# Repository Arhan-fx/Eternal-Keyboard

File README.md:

I am trying to create a good keyboard that will be replacing my current keyboard, and I will try my best to use keyboard forever so thats why I am naming it "eterna keyboard".

My plan is recycle my old 60% keeb and slam a new pcb, keys, and keycaps to make it usable again.

BOM
| Name                                                          | Qty | Final Price - INR (USD) | Link                                                                                                       |
| ------------------------------------------------------------- | --- | ----------------------- | ---------------------------------------------------------------------------------------------------------- |
| Gateron Milky yellow pro (Pack of 10)                         | 70  | 1500 ($17.20)           | (https://www.keebsmod.com/products/gateron-milky-yellow-pro?variant=46478287733034)                                                    |
| Ussixchare Keycaps 60 Percent 104 Backlit                     | 1   | 2400 ($27.14)           | (https://www.amazon.in/Ussixchare-Keyboard-Fullsize-Mechanical-Switches/dp/B092DGKYR4?th=1)                         |
| Diode 1N4148 Through - Hole                                   | 100 | 169 ($1.97)             | (https://amzn.in/d/j3eLvoh)                                                                          
| Orpheus Pico                                                  | 1   | Already owned           |
| Case for keyboard                                             | 1   | Recycling from ant esports mk1300mini with mods |
| PCB                                                           | 1   |1550 (17.50)             | (https://hc-cdn.hel1.your-objectstorage.com/s/v3/194ccc0d3551b167a0d77d0481acf72b9a564b7d_image.png)

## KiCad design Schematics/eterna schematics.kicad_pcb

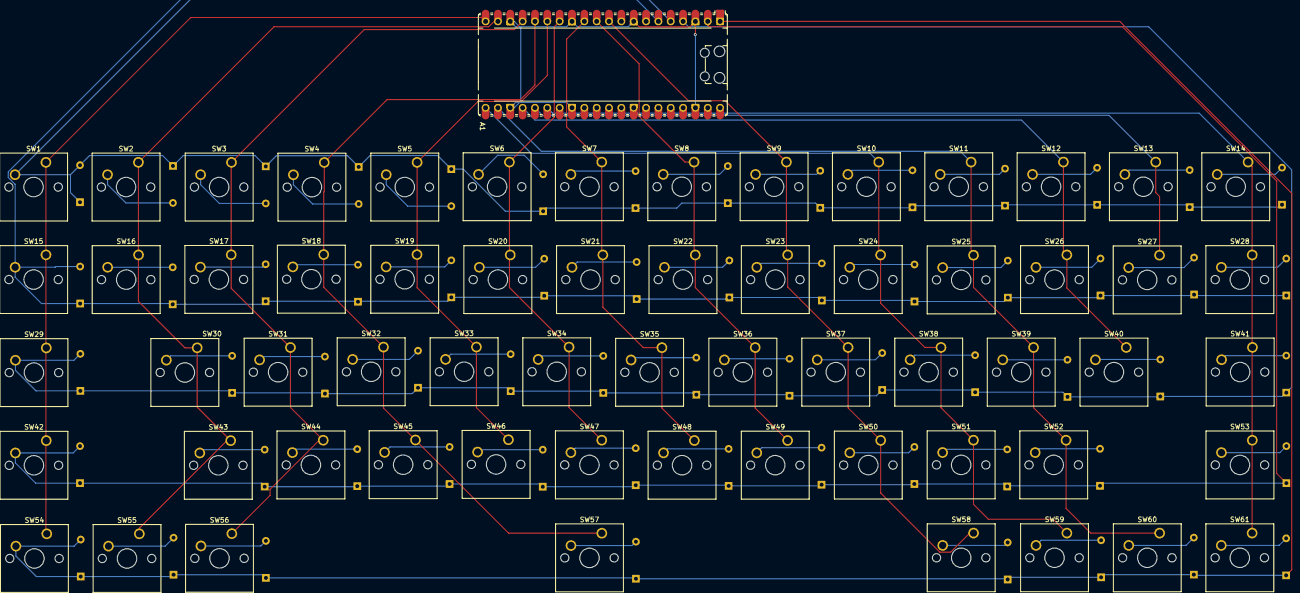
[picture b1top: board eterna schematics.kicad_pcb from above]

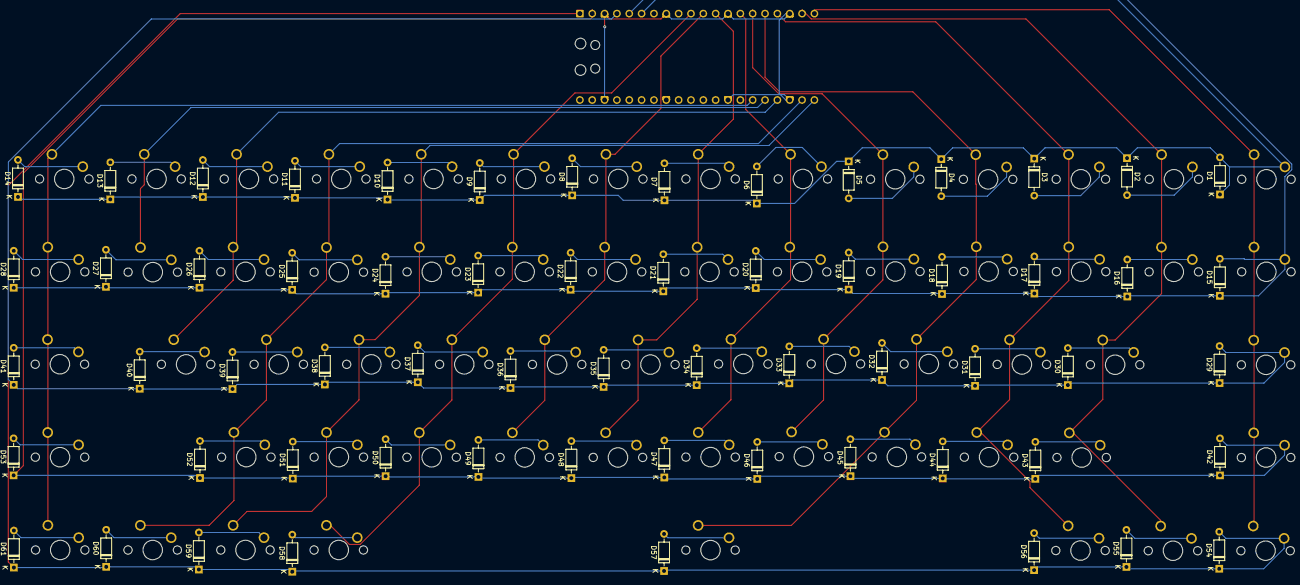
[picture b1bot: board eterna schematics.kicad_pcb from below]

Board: 2 copper layers, 123 parts (61 on the bottom side), 76 nets.

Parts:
A1: RaspberryPi_Pico; RaspberryPi_Pico_Common_Unspecified
D1, D2, D3, D4, D5, D6, D7, D8, D9, D10, D11, D12, D13, D14, D15, D16, D17, D18, D19, D20, D21, D22, D23, D24, D25, D26, D27, D28, D29, D30, D31, D32, D33, D34, D35, D36, D37, D38, D39, D40, D41, D42, D43, D44, D45, D46, D47, D48, D49, D50, D51, D52, D53, D54, D55, D56, D57, D58, D59, D60, D61: 1N4148; D_DO-35_SOD27_P7.62mm_Horizontal
SW1, SW2, SW3, SW4, SW5, SW6, SW7, SW8, SW9, SW10, SW11, SW12, SW13, SW14, SW15, SW16, SW17, SW18, SW19, SW20, SW21, SW22, SW23, SW24, SW25, SW26, SW27, SW28, SW29, SW30, SW31, SW32, SW33, SW34, SW35, SW36, SW37, SW38, SW39, SW40, SW41, SW42, SW43, SW44, SW45, SW46, SW47, SW48, SW49, SW50, SW51, SW52, SW53, SW54, SW55, SW56, SW57, SW58, SW59, SW60, SW61: SW_Push; SW_Cherry_MX_1.00u_PCB

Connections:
unnamed: A1.3 (GND), A1.8 (GND), A1.13 (GND), A1.18 (GND), A1.23 (GND), A1.28 (GND), A1.38 (GND)
unnamed: D2.2 (A), SW2.2
unnamed: D3.2 (A), SW3.2
unnamed: D4.2 (A), SW4.2
unnamed: D5.2 (A), SW5.2
unnamed: D6.2 (A), SW6.2
unnamed: D7.2 (A), SW7.2
unnamed: D8.2 (A), SW8.2
unnamed: D9.2 (A), SW9.2
unnamed: D10.2 (A), SW10.2
unnamed: D11.2 (A), SW11.2
unnamed: D12.2 (A), SW12.2
unnamed: D13.2 (A), SW13.2
unnamed: D14.2 (A), SW14.2
unnamed: D16.2 (A), SW16.2
unnamed: D17.2 (A), SW17.2
unnamed: D18.2 (A), SW18.2
unnamed: D19.2 (A), SW19.2
unnamed: D20.2 (A), SW20.2
unnamed: D21.2 (A), SW21.2
unnamed: D22.2 (A), SW22.2
unnamed: D23.2 (A), SW23.2
unnamed: D24.2 (A), SW24.2
unnamed: D25.2 (A), SW25.2
unnamed: D26.2 (A), SW26.2
unnamed: D27.2 (A), SW27.2
unnamed: D28.2 (A), SW28.2
unnamed: D30.2 (A), SW30.2
unnamed: D31.2 (A), SW31.2
unnamed: D32.2 (A), SW32.2
unnamed: D33.2 (A), SW33.2
unnamed: D34.2 (A), SW34.2
unnamed: D35.2 (A), SW35.2
unnamed: D36.2 (A), SW36.2
unnamed: D37.2 (A), SW37.2
unnamed: D38.2 (A), SW38.2
unnamed: D39.2 (A), SW39.2
unnamed: D40.2 (A), SW40.2
unnamed: D41.2 (A), SW41.2
unnamed: D43.2 (A), SW43.2
unnamed: D44.2 (A), SW44.2
unnamed: D45.2 (A), SW45.2
unnamed: D46.2 (A), SW46.2
unnamed: D47.2 (A), SW47.2
unnamed: D48.2 (A), SW48.2
unnamed: D49.2 (A), SW49.2
unnamed: D50.2 (A), SW50.2
unnamed: D51.2 (A), SW51.2
unnamed: D52.2 (A), SW52.2
unnamed: D53.2 (A), SW53.2
unnamed: D55.2 (A), SW55.2
unnamed: D56.2 (A), SW56.2
unnamed: D57.2 (A), SW57.2
unnamed: D58.2 (A), SW58.2
unnamed: D59.2 (A), SW59.2
unnamed: D60.2 (A), SW60.2
unnamed: D61.2 (A), SW61.2
col1: A1.20 (GPIO15), SW1.1, SW15.1, SW29.1, SW42.1, SW54.1
col2: A1.19 (GPIO14), SW2.1, SW16.1, SW30.1, SW43.1, SW55.1
col3: A1.17 (GPIO13), SW3.1, SW17.1, SW31.1, SW44.1, SW56.1
col4: A1.16 (GPIO12), SW4.1, SW18.1, SW32.1, SW45.1, SW57.1
col5: A1.15 (GPIO11), SW5.1, SW19.1, SW33.1, SW46.1
col6: A1.14 (GPIO10), SW6.1, SW20.1, SW34.1, SW47.1
col7: A1.12 (GPIO9), SW7.1, SW21.1, SW35.1, SW48.1
col8: A1.11 (GPIO8), SW8.1, SW22.1, SW36.1, SW49.1
col9: A1.10 (GPIO7), SW9.1, SW23.1, SW37.1, SW50.1, SW58.1
col10: A1.21 (GPIO16), SW10.1, SW24.1, SW38.1, SW51.1, SW59.1
col11: A1.22 (GPIO17), SW11.1, SW25.1, SW39.1, SW52.1, SW60.1
col12: A1.24 (GPIO18), SW12.1, SW26.1, SW40.1
col13: A1.25 (GPIO19), SW13.1, SW27.1
col14: A1.26 (GPIO20), SW14.1, SW28.1, SW41.1, SW53.1, SW61.1
row 1: A1.6 (GPIO4), D1.1 (K), D1.2 (A), D2.1 (K), D3.1 (K), D4.1 (K), D5.1 (K), D6.1 (K), D7.1 (K), D8.1 (K), D9.1 (K), D10.1 (K), D11.1 (K), D12.1 (K), D13.1 (K), D14.1 (K), SW1.2
row 2: A1.5 (GPIO3), D15.1 (K), D15.2 (A), D16.1 (K), D17.1 (K), D18.1 (K), D19.1 (K), D20.1 (K), D21.1 (K), D22.1 (K), D23.1 (K), D24.1 (K), D25.1 (K), D26.1 (K), D27.1 (K), D28.1 (K), SW15.2
row 3: A1.4 (GPIO2), D29.1 (K), D29.2 (A), D30.1 (K), D31.1 (K), D32.1 (K), D33.1 (K), D34.1 (K), D35.1 (K), D36.1 (K), D37.1 (K), D38.1 (K), D39.1 (K), D40.1 (K), D41.1 (K), SW29.2
row 4: A1.2 (GPIO1), D42.1 (K), D42.2 (A), D43.1 (K), D44.1 (K), D45.1 (K), D46.1 (K), D47.1 (K), D48.1 (K), D49.1 (K), D50.1 (K), D51.1 (K), D52.1 (K), D53.1 (K), SW42.2
row 5: A1.1 (GPIO0), D54.1 (K), D54.2 (A), D55.1 (K), D56.1 (K), D57.1 (K), D58.1 (K), D59.1 (K), D60.1 (K), D61.1 (K), SW54.2

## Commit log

2025-10-10 Create a
2025-10-10 Create Production screenshot
2025-10-10 Rename readme to readme.md
2025-10-10 Rename eterna schematics.csv to bom.csv
2025-10-10 Rename readme.md to README.md
